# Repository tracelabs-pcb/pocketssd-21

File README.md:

# PocketSSD-21 — Kompakter USB 3.2 Gen2 NVMe Adapter

**Status: PCB-Design abgeschlossen — unbestückt**  
**Tool:** KiCad | **Layer:** 6-Layer | **Hersteller-ready:** Ja

---

## Projektbeschreibung

Kompakter USB 3.2 Gen2 zu NVMe M.2 Bridge-Adapter auf Basis des JMS583.
Designed für maximale Datenrate bei minimaler Baugröße. 
6-Layer-Stackup (JLC06161H-1080) für saubere Signalintegrität auf 
USB 3.2 Gen2 SuperSpeed+ und PCIe-Leiterbahnen.

**Besonderheiten:**
- USB 3.2 Gen2 (10 Gbit/s) über USB-C
- NVMe M.2 (PCIe Gen3 ×2) Unterstützung
- JMS583 Bridge-Controller
- Differentielle Paare mit kontrollierter Impedanz
- Kompaktes Format, direkt steckbar

---

## Hardware

| Komponente | Beschreibung |
|---|---|
| Bridge-Controller | JMS583 (USB 3.2 Gen2 ↔ PCIe Gen3 ×2) |
| Schnittstelle Host | USB-C (USB 3.2 Gen2, 10 Gbit/s) |
| Schnittstelle Storage | M.2 Key-M (NVMe, PCIe Gen3 ×2) |
| Stackup | 6-Layer (JLC06161H-1080) |
| Tool | KiCad |

---

## PCB

- 6-Layer Stackup für kontrollierte Impedanz
- Differentielle Paare (USB SS+/−, PCIe TX/RX) mit Längen-Matching
- Dedizierte GND-Planes zur Schirmung
- Hierarchisches Schematic über fünf Sheets

---

## Ausschlüsse

Portfolioprojekt — kein Serienprodukt, kein CE/EMV.

---

## Dateien in diesem Repository

- `/kicad/` — KiCad Projektdateien
- `/screenshots/` — PCB- und Schematic-Ansichten

---

> Entwickelt von [Shawn Schneider](https://tracelabs-pcb.de)  
> — PCB-Design & Lötservice, Wolfsburg

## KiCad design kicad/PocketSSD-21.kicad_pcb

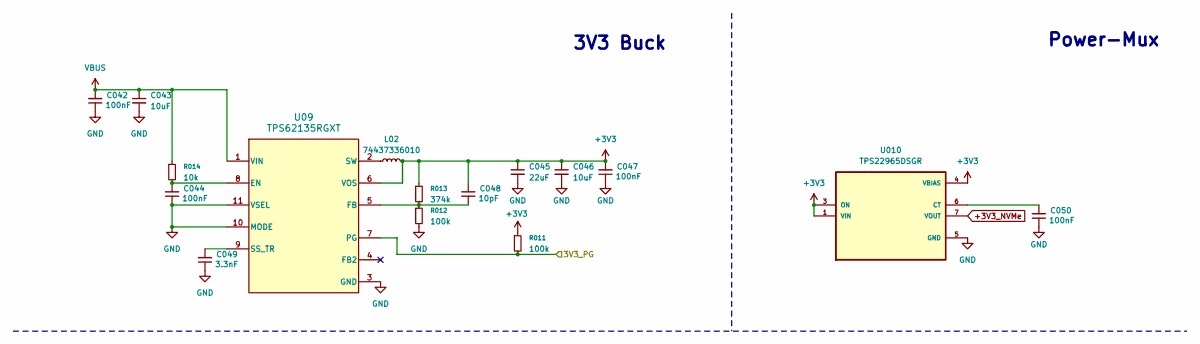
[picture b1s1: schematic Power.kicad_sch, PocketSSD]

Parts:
C042, C044, C047, C050: 100nF; C_0201_0603Metric
C043, C046: 10uF; C_0402_1005Metric
C045: 22uF; C_0402_1005Metric
C048: 10pF; C_0201_0603Metric
C049: 3.3nF; C_0201_0603Metric
L02: 74437336010; WE-LHMI_5030
R011, R012: 100k; R_0201_0603Metric
R013: 374k; R_0201_0603Metric
R014: 10k; R_0201_0603Metric
U09: TPS62135RGXT; RGX0011A
U010: TPS22965DSGR; SON50P200X200X80-9N

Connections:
+3V3: C045.1, C046.1, C047.2, C048.2, L02.2, R011.1, R013.1, U09.6 (VOS), U010.1 (VIN), U010.2 (VIN), U010.3 (ON), U010.4 (VBIAS); also elsewhere on the board
+3V3_NVMe: U010.7 (VOUT), U010.8 (VOUT); also elsewhere on the board
/Bridge_JMS583/3V3_PG: R011.2, U09.7 (PG); also elsewhere on the board
GND: C042.1, C043.2, C044.1, C045.2, C046.2, C047.1, C049.1, C050.1, R012.2, U09.3 (GND), U09.10 (MODE), U09.11 (VSEL), U010.5 (GND), U010.9 (GND), U010.9_1 (GND), U010.9_2 (GND); also elsewhere on the board
unnamed: C044.2, R014.2, U09.8 (EN)
unnamed: C048.1, R012.1, R013.2, U09.5 (FB)
unnamed: C049.2, U09.9 (SS_TR)
unnamed: L02.1, U09.2 (SW)
unnamed: C050.2, U010.6 (CT)
VBUS: C042.2, C043.1, R014.1, U09.1 (VIN); also elsewhere on the board

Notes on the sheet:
Power-Mux
3V3 Buck

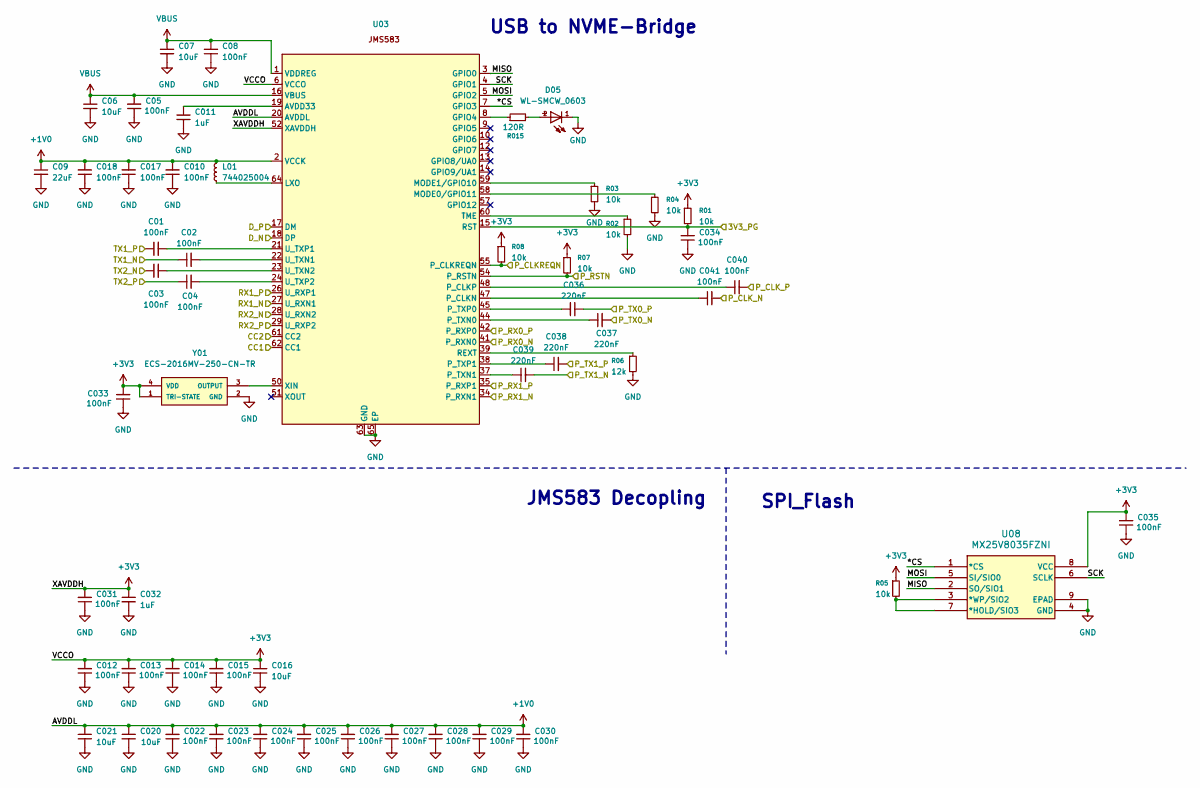
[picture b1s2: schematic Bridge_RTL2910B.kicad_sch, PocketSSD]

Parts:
C01, C02, C03, C04, C05, C08, C010, C012, C013, C014, C015, C017, C018, C022, C023, C024, C025, C026, C027, C028, C029, C030, C031, C033, C034, C035, C040, C041: 100nF; C_0201_0603Metric
C06, C07, C016, C020, C021: 10uF; C_0402_1005Metric
C09: 22uF; C_0402_1005Metric
C011, C032: 1uF; C_0402_1005Metric
C036, C037, C038, C039: 220nF; C_0201_0603Metric
D05: WL-SMCW_0603
L01: 744025004; WE-TPC_2828
R01, R02, R03, R04, R05, R07, R08: 10k; R_0201_0603Metric
R06: 12k; R_0201_0603Metric
R015: 120R; R_0201_0603Metric
U03: IC_KSZ8794CNXCC-TR
U08: MX25V8035FZNI; WSON8_6X5_MAC
Y01: ECS-2016MV-250-CN-TR; OSC_ECS-1618-300-BN-TR

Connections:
+1V0: C09.1, C010.2, C017.2, C018.2, C020.1, C021.1, C022.2, C023.2, C024.2, C025.2, C026.2, C027.2, C028.2, C029.2, C030.2, L01.2, U03.2 (VCCK), U03.20 (AVDDL), U03.25 (U_AVDDL), U03.30 (U_AVDDL), U03.31 (VCCK), U03.33 (P_AVDDL), U03.36 (P_AVDDL), U03.40 (P_AVDDL), U03.43 (P_AVDDL), U03.46 (C_AVDDL), U03.49 (P_AVDDL), U03.53 (VCCK)
+3V3: C012.2, C013.2, C014.2, C015.2, C016.1, C031.2, C032.1, C033.2, C035.2, R01.1, R05.1, R07.1, R08.1, U03.6 (VCCO), U03.11 (VCCO), U03.32 (VCCO), U03.52 (XAVDDH), U03.56 (VCCO), U08.8 (VCC), Y01.1 (TRI-STATE), Y01.4 (VDD); also elsewhere on the board
/Bridge_JMS583/3V3_PG: C034.2, R01.2, U03.15 (RST); also elsewhere on the board
/Bridge_JMS583/*CS: U03.7 (GPIO3), U08.1 (*CS)
/Bridge_JMS583/CC1: U03.62 (CC1); also elsewhere on the board
/Bridge_JMS583/CC2: U03.61 (CC2); also elsewhere on the board
/Bridge_JMS583/D_N: U03.18 (DP); also elsewhere on the board
/Bridge_JMS583/D_P: U03.17 (DM); also elsewhere on the board
/Bridge_JMS583/MISO: U03.3 (GPIO0), U08.2 (SO/SIO1)
/Bridge_JMS583/MOSI: U03.5 (GPIO2), U08.5 (SI/SIO0)
/Bridge_JMS583/P_CLKREQN: R08.2, U03.55 (P_CLKREQN); also elsewhere on the board
/Bridge_JMS583/P_CLK_N: C041.2; also elsewhere on the board
/Bridge_JMS583/P_CLK_P: C040.2; also elsewhere on the board
/Bridge_JMS583/P_RSTN: R07.2, U03.54 (P_RSTN); also elsewhere on the board
/Bridge_JMS583/P_RX0_N: U03.41 (P_RXN0); also elsewhere on the board
/Bridge_JMS583/P_RX0_P: U03.42 (P_RXP0); also elsewhere on the board
/Bridge_JMS583/P_RX1_N: U03.34 (P_RXN1); also elsewhere on the board
/Bridge_JMS583/P_RX1_P: U03.35 (P_RXP1); also elsewhere on the board
/Bridge_JMS583/P_TX0_N: C037.2; also elsewhere on the board
/Bridge_JMS583/P_TX0_P: C036.2; also elsewhere on the board
/Bridge_JMS583/P_TX1_N: C039.2; also elsewhere on the board
/Bridge_JMS583/P_TX1_P: C038.2; also elsewhere on the board
/Bridge_JMS583/RX1_N: U03.27 (U_RXN1); also elsewhere on the board
/Bridge_JMS583/RX1_P: U03.26 (U_RXP1); also elsewhere on the board
/Bridge_JMS583/RX2_N: U03.28 (U_RXN2); also elsewhere on the board
/Bridge_JMS583/RX2_P: U03.29 (U_RXP2); also elsewhere on the board
/Bridge_JMS583/SCK: U03.4 (GPIO1), U08.6 (SCLK)
/Bridge_JMS583/TX1_N: C02.1; also elsewhere on the board
/Bridge_JMS583/TX1_P: C01.1; also elsewhere on the board
/Bridge_JMS583/TX2_N: C03.1; also elsewhere on the board
/Bridge_JMS583/TX2_P: C04.1; also elsewhere on the board
GND: C05.1, C06.2, C07.2, C08.1, C09.2, C010.1, C011.2, C012.1, C013.1, C014.1, C015.1, C016.2, C017.1, C018.1, C020.2, C021.2, C022.1, C023.1, C024.1, C025.1, C026.1, C027.1, C028.1, C029.1, C030.1, C031.1, C032.2, C033.1, C034.1, C035.1, D05.1, R02.2, R03.2, R04.2, R06.2, U03.63 (GND), U03.65 (EP), U03.66 (GND), U03.67 (GND), U03.68 (GND), U03.69 (GND), U03.70 (GND), U03.71 (GND), U03.72 (GND), U03.73 (GND), U03.74 (GND), U03.75 (GND), U03.76 (GND), U03.77 (GND), U03.78 (GND), U03.79 (GND), U03.80 (GND), U03.81 (GND), U08.4 (GND), U08.9 (EPAD), Y01.2 (GND); also elsewhere on the board
unnamed: D05.2, R015.2
unnamed: C011.1, U03.19 (AVDD33)
unnamed: R015.1, U03.8 (GPIO4)
unnamed: L01.1, U03.64 (LXO)
unnamed: R04.1, U03.58 (MODE0/GPIO11)
unnamed: R03.1, U03.59 (MODE1/GPIO10)
unnamed: C041.1, U03.47 (P_CLKN)
unnamed: C040.1, U03.48 (P_CLKP)
unnamed: C037.1, U03.44 (P_TXN0)
unnamed: C039.1, U03.37 (P_TXN1)
unnamed: C036.1, U03.45 (P_TXP0)
unnamed: C038.1, U03.38 (P_TXP1)
unnamed: R06.1, U03.39 (REXT)
unnamed: R02.1, U03.60 (TME)
unnamed: C02.2, U03.22 (U_TXN1)
unnamed: C03.2, U03.23 (U_TXN2)
unnamed: C01.2, U03.21 (U_TXP1)
unnamed: C04.2, U03.24 (U_TXP2)
unnamed: U03.50 (XIN), Y01.3 (OUTPUT)
unnamed: R05.2, U08.3 (*WP/SIO2), U08.7 (*HOLD/SIO3)
VBUS: C05.2, C06.1, C07.1, C08.2, U03.1 (VDDREG), U03.16 (VBUS); also elsewhere on the board

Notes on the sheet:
JMS583 Decopling
USB to NVME-Bridge
SPI_Flash

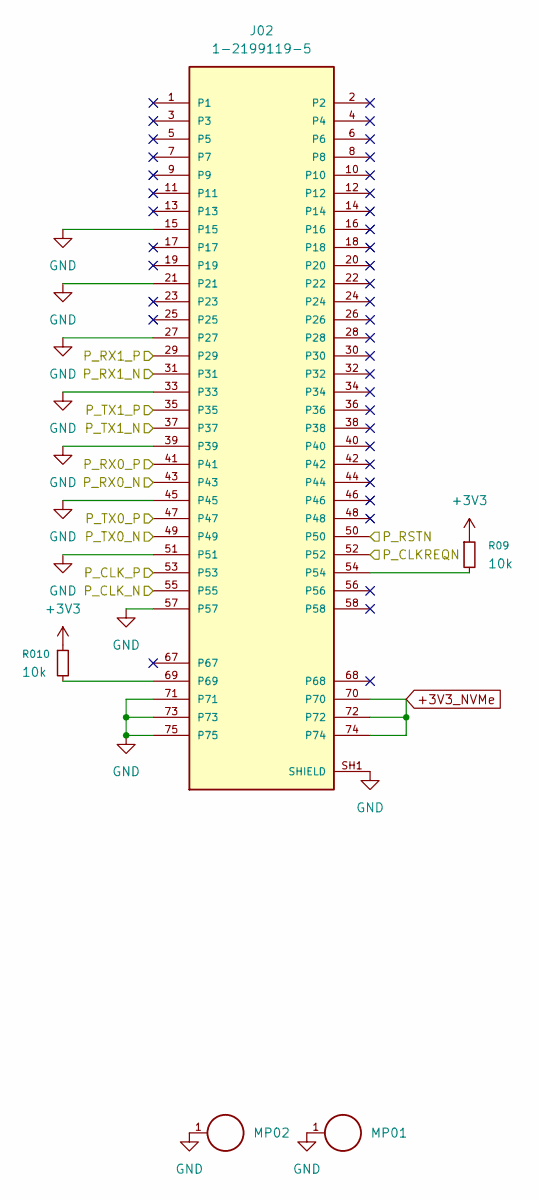
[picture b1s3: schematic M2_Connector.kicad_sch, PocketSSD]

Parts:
J02: 1-2199119-5; TE_1-2199119-5; DigiKey_Part_Number A115902CT-ND
MP01, MP02: M2.5 x 2.5mm; WA-SMSI_9774025151; PART-NUMBER 9774025151R
R09, R010: 10k; R_0201_0603Metric

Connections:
+3V3: R09.1, R010.1; also elsewhere on the board
+3V3_NVMe: J02.70, J02.72, J02.74; also elsewhere on the board
/Bridge_JMS583/P_CLKREQN: J02.52; also elsewhere on the board
/Bridge_JMS583/P_CLK_N: J02.55; also elsewhere on the board
/Bridge_JMS583/P_CLK_P: J02.53; also elsewhere on the board
/Bridge_JMS583/P_RSTN: J02.50; also elsewhere on the board
/Bridge_JMS583/P_RX0_N: J02.43; also elsewhere on the board
/Bridge_JMS583/P_RX0_P: J02.41; also elsewhere on the board
/Bridge_JMS583/P_RX1_N: J02.31; also elsewhere on the board
/Bridge_JMS583/P_RX1_P: J02.29; also elsewhere on the board
/Bridge_JMS583/P_TX0_N: J02.49; also elsewhere on the board
/Bridge_JMS583/P_TX0_P: J02.47; also elsewhere on the board
/Bridge_JMS583/P_TX1_N: J02.37; also elsewhere on the board
/Bridge_JMS583/P_TX1_P: J02.35; also elsewhere on the board
GND: J02.15, J02.21, J02.27, J02.33, J02.39, J02.45, J02.51, J02.57, J02.71, J02.73, J02.75, J02.SH1 (SHIELD), J02.SH2 (SHIELD), MP01.1, MP02.1; also elsewhere on the board
unnamed: J02.54, R09.2
unnamed: J02.69, R010.2

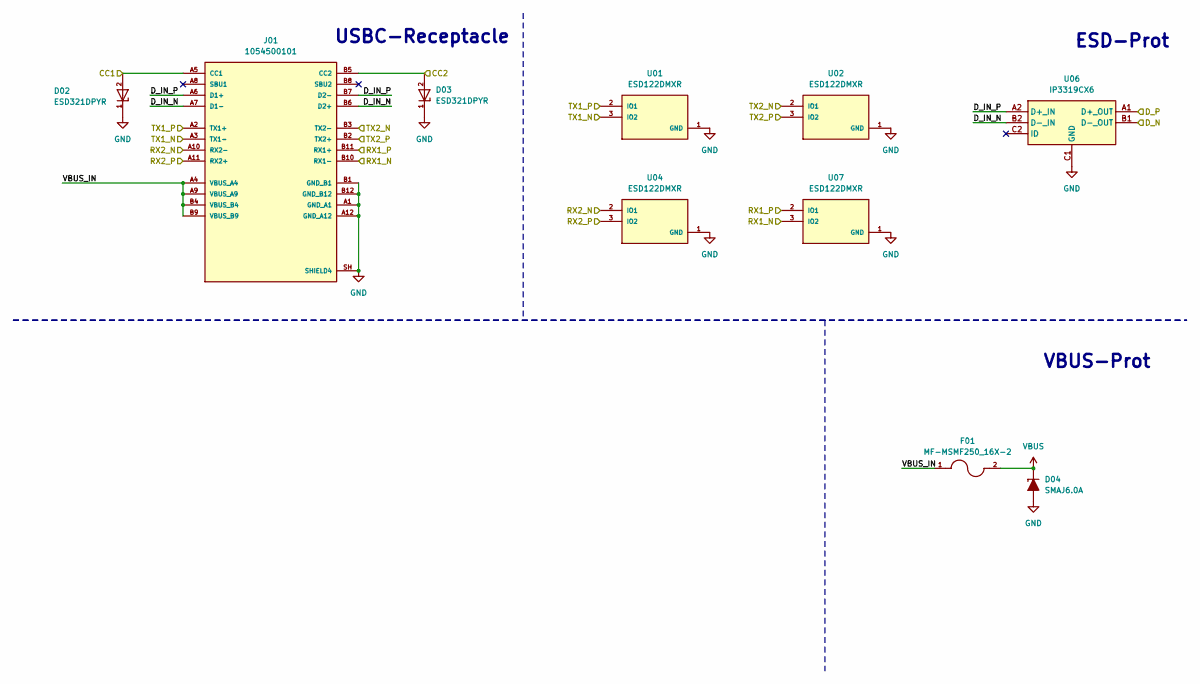
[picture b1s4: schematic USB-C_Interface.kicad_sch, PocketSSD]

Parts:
D02, D03: ESD321DPYR; TVS_ESD321DPYR; PARTREV B
D04: SMAJ6.0A; D_SMA
F01: MF-MSMF250_16X-2; FUSER_MF-MSMF250_16X-2
J01: 1054500101; USB_C_Receptacle_Molex_105450-0101; PARTREV A7
U01, U02, U04, U07: ESD122DMXR; IC_ESD122DMXR; PARTREV A
U06: IP3319CX6; WLCSP-6_1.4x1.0mm_P0.4mm

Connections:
/Bridge_JMS583/CC1: D02.2, J01.A5 (CC1); also elsewhere on the board
/Bridge_JMS583/CC2: D03.2, J01.B5 (CC2); also elsewhere on the board
/Bridge_JMS583/D_N: U06.B1 (D-_OUT); also elsewhere on the board
/Bridge_JMS583/D_P: U06.A1 (D+_OUT); also elsewhere on the board
/Bridge_JMS583/RX1_N: J01.B10 (RX1-), U07.3 (IO2); also elsewhere on the board
/Bridge_JMS583/RX1_P: J01.B11 (RX1+), U07.2 (IO1); also elsewhere on the board
/Bridge_JMS583/RX2_N: J01.A10 (RX2-), U04.2 (IO1); also elsewhere on the board
/Bridge_JMS583/RX2_P: J01.A11 (RX2+), U04.3 (IO2); also elsewhere on the board
/Bridge_JMS583/TX1_N: J01.A3 (TX1-), U01.3 (IO2); also elsewhere on the board
/Bridge_JMS583/TX1_P: J01.A2 (TX1+), U01.2 (IO1); also elsewhere on the board
/Bridge_JMS583/TX2_N: J01.B3 (TX2-), U02.2 (IO1); also elsewhere on the board
/Bridge_JMS583/TX2_P: J01.B2 (TX2+), U02.3 (IO2); also elsewhere on the board
/USB-C_Interface/D_IN_N: J01.A7 (D1-), J01.B6 (D2+), U06.B2 (D-_IN)
/USB-C_Interface/D_IN_P: J01.A6 (D1+), J01.B7 (D2-), U06.A2 (D+_IN)
/USB-C_Interface/VBUS_IN: F01.1, J01.A4 (VBUS_A4), J01.A9 (VBUS_A9), J01.B4 (VBUS_B4), J01.B9 (VBUS_B9)
GND: D02.1, D03.1, D04.2 (A), J01.A1 (GND_A1), J01.A12 (GND_A12), J01.B1 (GND_B1), J01.B12 (GND_B12), J01.SH (SHIELD4), U01.1 (GND), U02.1 (GND), U04.1 (GND), U06.C1 (GND), U07.1 (GND); also elsewhere on the board
VBUS: D04.1 (K), F01.2; also elsewhere on the board

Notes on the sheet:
VBUS-Prot
ESD-Prot
USBC-Receptacle

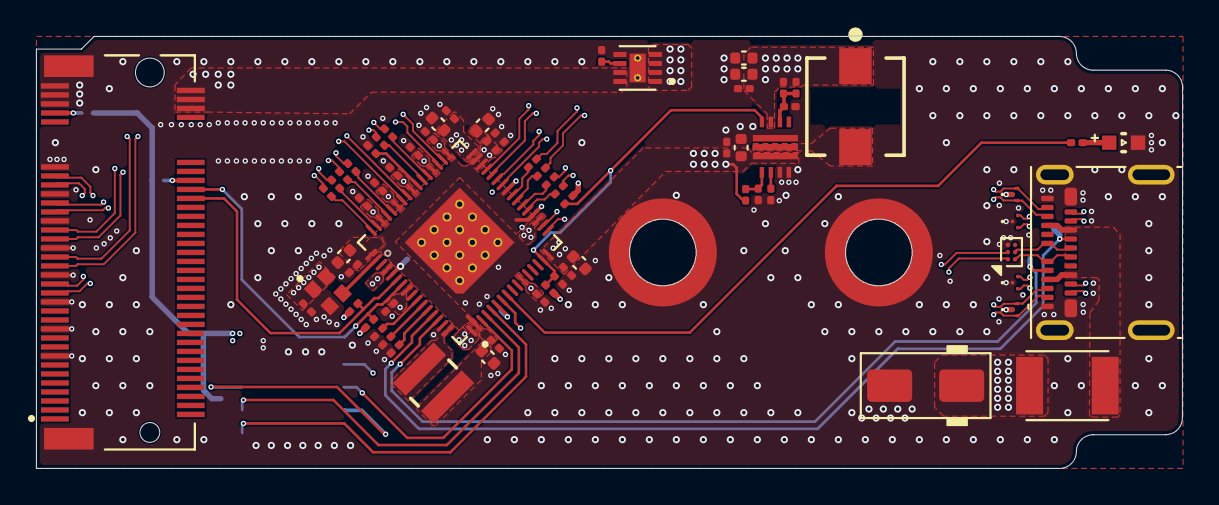
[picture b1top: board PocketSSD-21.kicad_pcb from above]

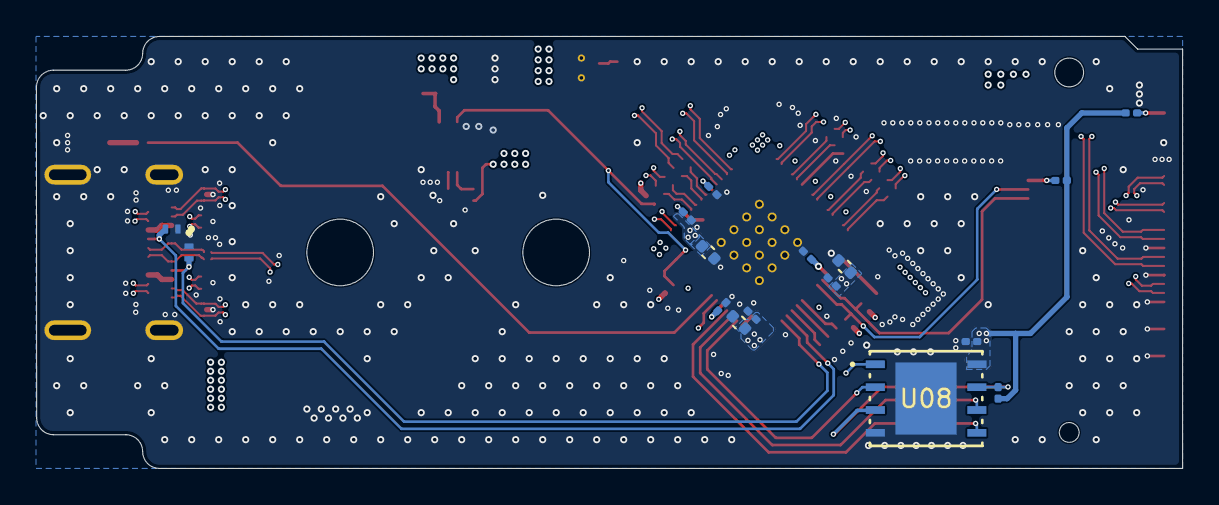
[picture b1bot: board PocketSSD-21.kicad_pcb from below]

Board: 6 copper layers, 63.7 x 24.0 mm, 85 parts (16 on the bottom side), 64 nets.

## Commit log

2026-06-25 Add screenshots folder
2026-06-25 Add project screenshots
2026-06-25 Add kicad folder
2026-06-25 Add KiCad project files
